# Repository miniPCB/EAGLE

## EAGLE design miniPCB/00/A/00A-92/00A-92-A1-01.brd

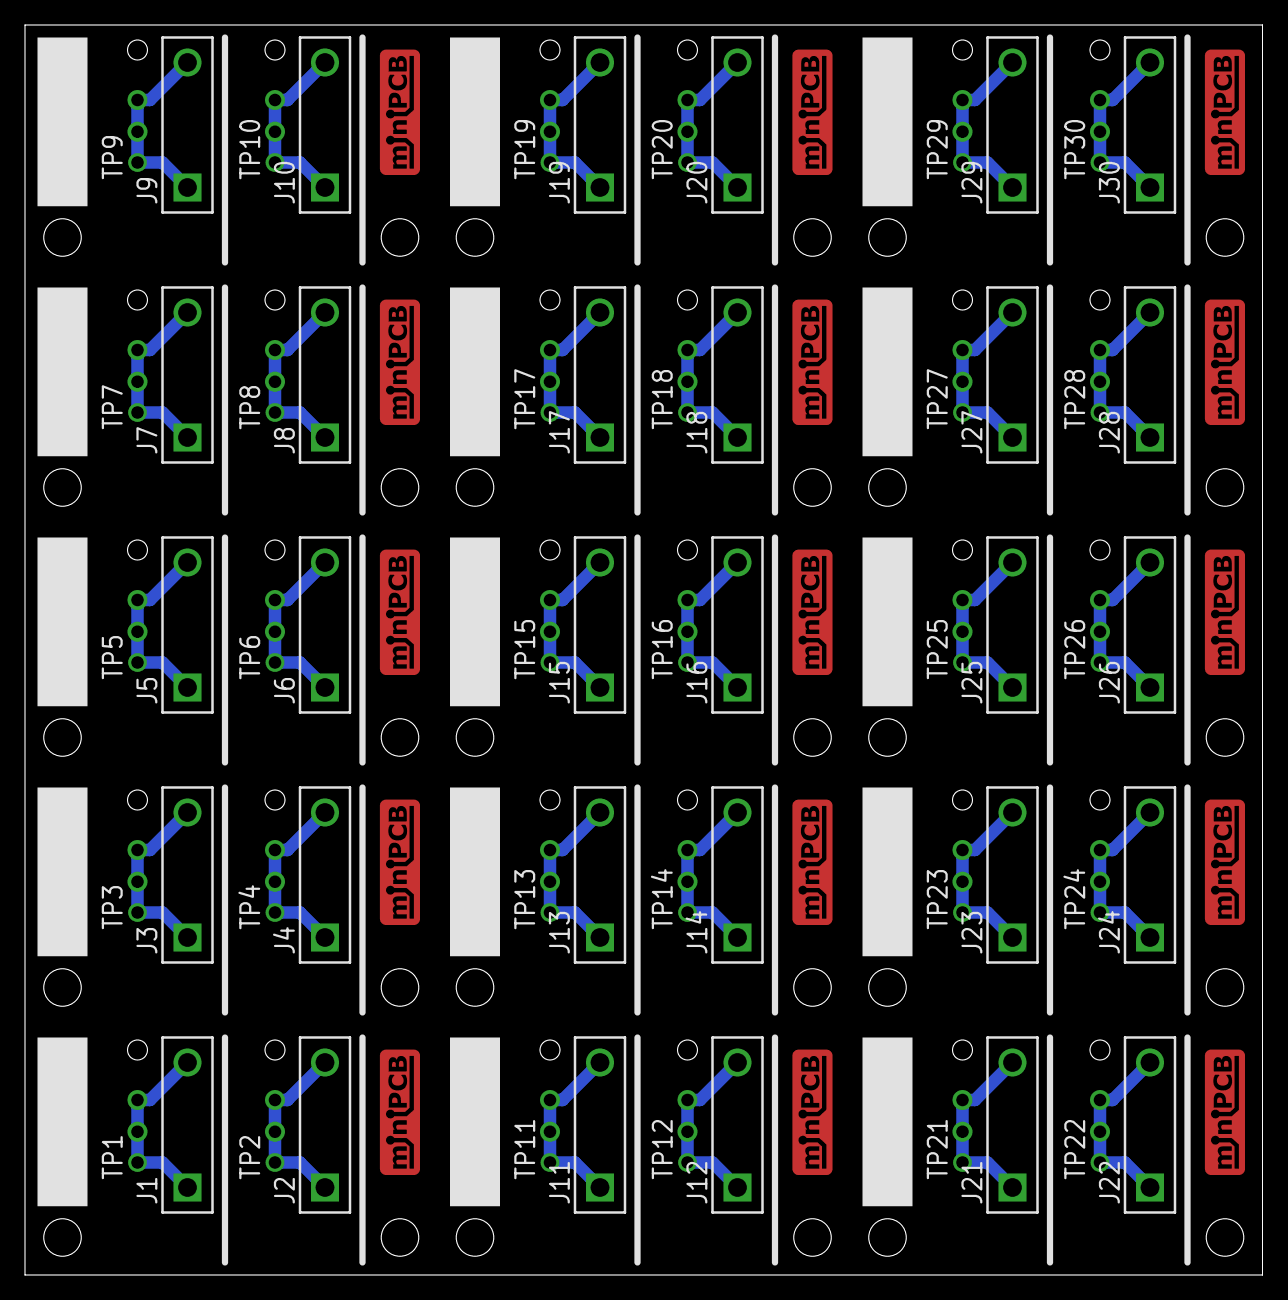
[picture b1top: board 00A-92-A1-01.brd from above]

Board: 2 copper layers, 99.0 x 100.0 mm, 106 parts (0 on the bottom side), 30 nets.

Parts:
E$1: MINIPCB_PANEL_IMAGEFRAME
J1, J2, J3, J4, J5, J6, J7, J8, J9, J10, J11, J12, J13, J14, J15, J16, J17, J18, J19, J20, J21, J22, J23, J24, J25, J26, J27, J28, J29, J30: PINS_1_KE6060
P1, P2, P3, P4, P5, P6, P7, P8, P9, P10, P11, P12, P13, P14, P15, P16, P17, P18, P19, P20, P21, P22, P23, P24, P25, P26, P27, P28, P29, P30: PINS_1_1MM-NOTEXT
PCB1, PCB2, PCB3, PCB4, PCB5, PCB6, PCB7, PCB8, PCB9, PCB10, PCB11, PCB12, PCB13, PCB14, PCB15: MINIPCB_00A_20X33
TP1, TP2, TP3, TP4, TP5, TP6, TP7, TP8, TP9, TP10, TP11, TP12, TP13, TP14, TP15, TP16, TP17, TP18, TP19, TP20, TP21, TP22, TP23, TP24, TP25, TP26, TP27, TP28, TP29, TP30: PINS_1_TESTPOINT_KE5000_NOTEXT

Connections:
unnamed: J1.1, J1.2, P1.1, P1.2, TP1.1
unnamed: J3.1, J3.2, P3.1, P3.2, TP3.1
unnamed: J2.1, J2.2, P2.1, P2.2, TP2.1
unnamed: J4.1, J4.2, P4.1, P4.2, TP4.1
unnamed: J5.1, J5.2, P5.1, P5.2, TP5.1
unnamed: J6.1, J6.2, P6.1, P6.2, TP6.1
unnamed: J7.1, J7.2, P7.1, P7.2, TP7.1
unnamed: J8.1, J8.2, P8.1, P8.2, TP8.1
unnamed: J9.1, J9.2, P9.1, P9.2, TP9.1
unnamed: J10.1, J10.2, P10.1, P10.2, TP10.1
unnamed: J11.1, J11.2, P11.1, P11.2, TP11.1
unnamed: J12.1, J12.2, P12.1, P12.2, TP12.1
unnamed: J13.1, J13.2, P13.1, P13.2, TP13.1
unnamed: J14.1, J14.2, P14.1, P14.2, TP14.1
unnamed: J15.1, J15.2, P15.1, P15.2, TP15.1
unnamed: J16.1, J16.2, P16.1, P16.2, TP16.1
unnamed: J17.1, J17.2, P17.1, P17.2, TP17.1
unnamed: J18.1, J18.2, P18.1, P18.2, TP18.1
unnamed: J19.1, J19.2, P19.1, P19.2, TP19.1
unnamed: J20.1, J20.2, P20.1, P20.2, TP20.1
unnamed: J21.1, J21.2, P21.1, P21.2, TP21.1
unnamed: J22.1, J22.2, P22.1, P22.2, TP22.1
unnamed: J23.1, J23.2, P23.1, P23.2, TP23.1
unnamed: J24.1, J24.2, P24.1, P24.2, TP24.1
unnamed: J25.1, J25.2, P25.1, P25.2, TP25.1
unnamed: J26.1, J26.2, P26.1, P26.2, TP26.1
unnamed: J27.1, J27.2, P27.1, P27.2, TP27.1
unnamed: J28.1, J28.2, P28.1, P28.2, TP28.1
unnamed: J29.1, J29.2, P29.1, P29.2, TP29.1
unnamed: J30.1, J30.2, P30.1, P30.2, TP30.1

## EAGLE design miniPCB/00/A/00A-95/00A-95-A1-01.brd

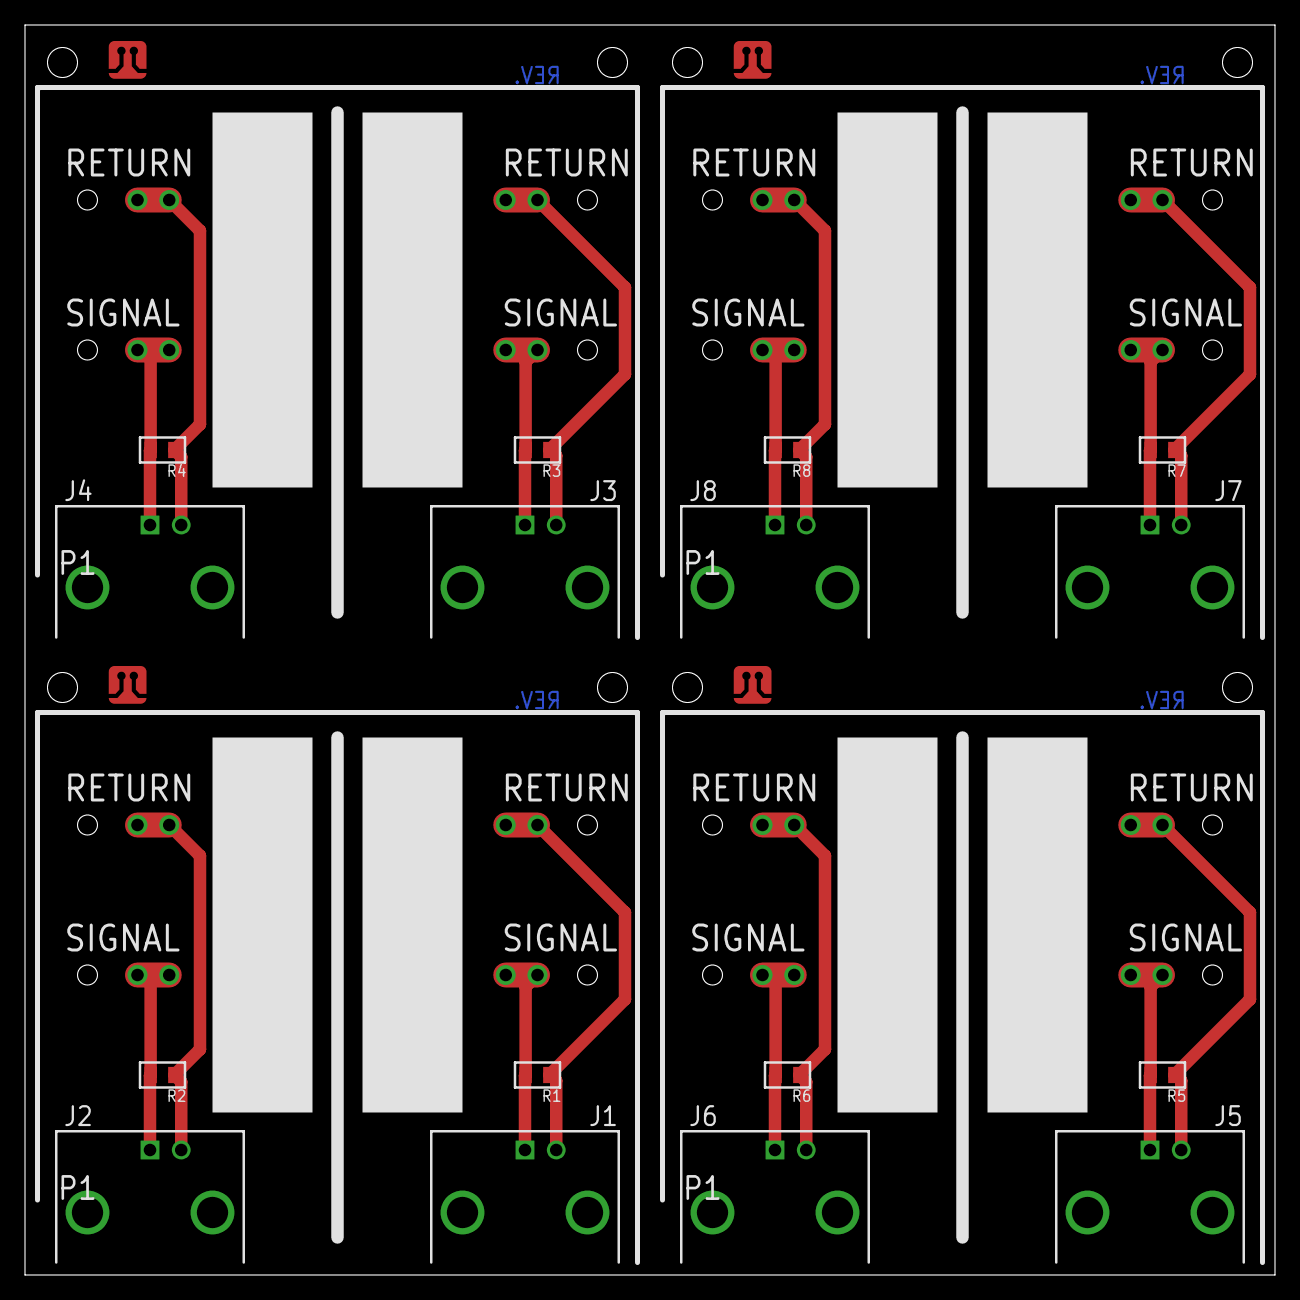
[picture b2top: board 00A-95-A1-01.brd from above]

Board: 2 copper layers, 100.0 x 100.0 mm, 37 parts (0 on the bottom side), 16 nets.

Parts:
E$1: MINIPCB_PANEL_IMAGEFRAME
J1, J2, J3, J4, J5, J6, J7, J8: BNC_RIGHTANGLE
P1, P2, P3, P4, P5, P6, P7, P8, P9, P10, P11, P12, P13, P14, P15, P16: PINS_1_1MM-NOTEXT
PCB1, PCB2, PCB3, PCB4: MINIPCB_0P_50X50MM
R1, R3, R5, R7: 100; R0805
R2, R4, R6, R8: 50; R0805

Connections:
unnamed: J2.1, P3.1, P3.2, R2.2
unnamed: J2.2, P4.1, P4.2, R2.1
unnamed: J1.1, P1.1, P1.2, R1.2
unnamed: J1.2, P2.1, P2.2, R1.1
unnamed: J4.1, P7.1, P7.2, R4.2
unnamed: J4.2, P8.1, P8.2, R4.1
unnamed: J3.1, P5.1, P5.2, R3.2
unnamed: J3.2, P6.1, P6.2, R3.1
unnamed: J6.1, P11.1, P11.2, R6.2
unnamed: J6.2, P12.1, P12.2, R6.1
unnamed: J5.1, P9.1, P9.2, R5.2
unnamed: J5.2, P10.1, P10.2, R5.1
unnamed: J8.1, P15.1, P15.2, R8.2
unnamed: J8.2, P16.1, P16.2, R8.1
unnamed: J7.1, P13.1, P13.2, R7.2
unnamed: J7.2, P14.1, P14.2, R7.1

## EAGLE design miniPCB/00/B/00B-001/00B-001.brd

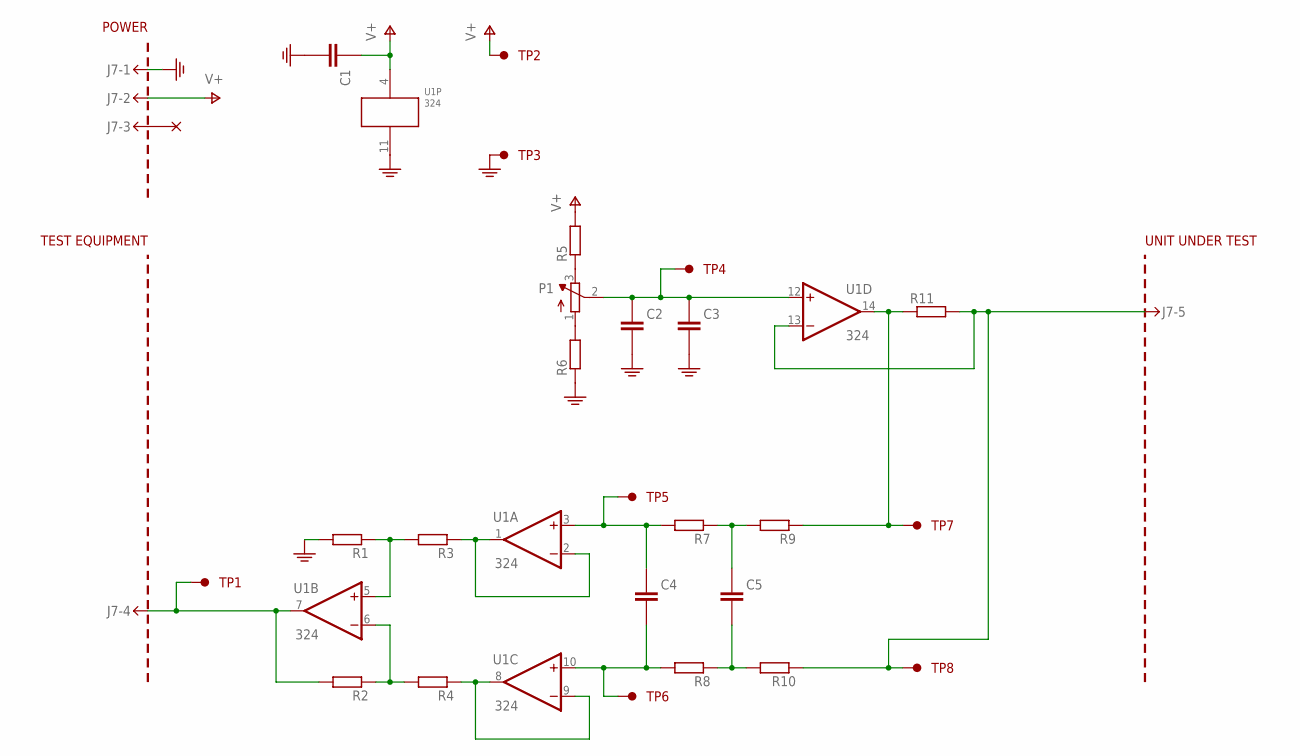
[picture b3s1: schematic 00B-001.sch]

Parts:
C1: 1u; C050-024X044
C2: CAPACITOR_10; C5MM
C3, C4, C5: CAPACITORTHD; C050-024X044
J7-: MINIPCB_5P50X50; MINIPCB_5P_50X50MM; PART_NUMBER 00B-001
P1: TRIMPOT0.100THD; TRIM_0100
R1, R2, R3, R4, R5, R6, R7, R8, R9, R10, R11: RESISTOR10MM; 0207/10
TP1, TP2, TP3, TP4, TP5, TP6, TP7, TP8: TESTPOINTKE5000-SMTEXT; PINS_1_TESTPOINT_KE5000_NOTEXT
U1: 324; DIL14

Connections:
GND: C1.2 (-), C2.-, C3.2 (-), J7-.1, R1.2, R6.1, TP3.1, U1.11 (V-)
unnamed: R9.1, R11.1, TP7.1, U1.14 (OUT)
unnamed: R3.1, U1.1 (OUT), U1.2 (-IN)
unnamed: R4.1, U1.8 (OUT), U1.9 (-IN)
unnamed: C2.+, C3.1 (+), P1.2 (S), TP4.1, U1.12 (+IN)
unnamed: P1.1 (A), R6.2
unnamed: P1.3 (E), R5.1
unnamed: J7-.5, R10.1, R11.2, TP8.1, U1.13 (-IN)
unnamed: R2.1, R4.2, U1.6 (-IN)
unnamed: R1.1, R3.2, U1.5 (+IN)
unnamed: J7-.4, R2.2, TP1.1, U1.7 (OUT)
unnamed: C4.1 (+), R7.2, TP5.1, U1.3 (+IN)
unnamed: C4.2 (-), R8.2, TP6.1, U1.10 (+IN)
unnamed: C5.1 (+), R7.1, R9.2
unnamed: C5.2 (-), R8.1, R10.2
V+: C1.1 (+), J7-.2, R5.2, TP2.1, U1.4 (V+)

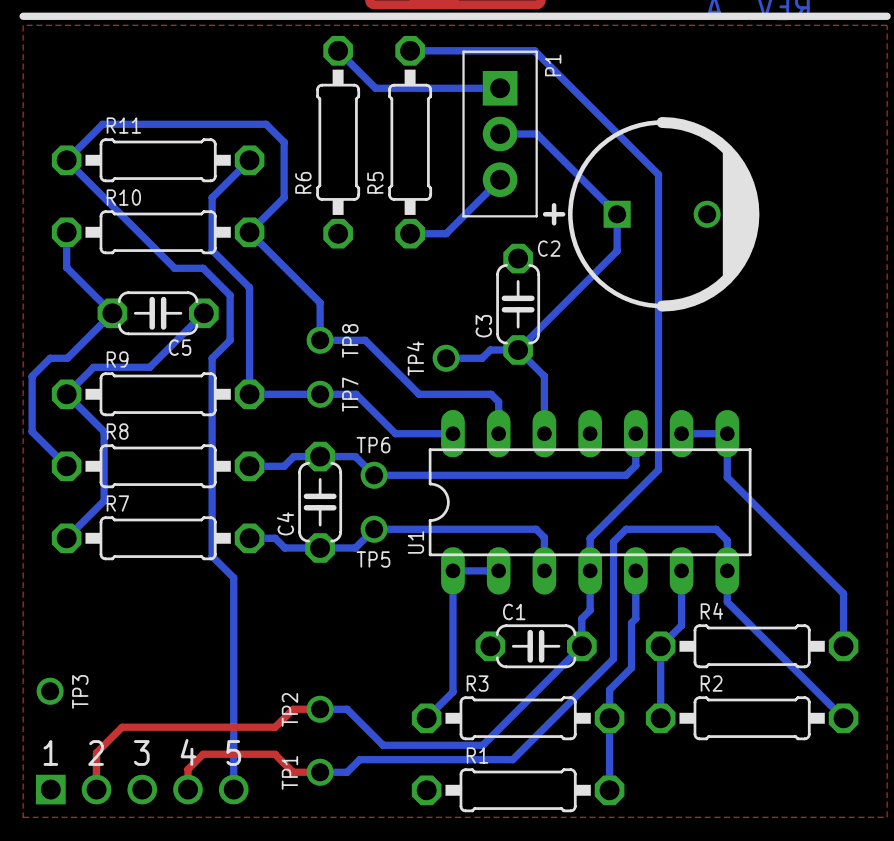
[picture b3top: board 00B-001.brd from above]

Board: 2 copper layers, 27 parts (0 on the bottom side), 16 nets.
